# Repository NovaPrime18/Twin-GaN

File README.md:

# Twin-GaN

**Dual 3-phase GaN motor controller with on-board CAN traction control**

---

## Overview

Twin-GaN is an open-source, dual-motor VESC-compatible controller that fits two complete 3-phase inverters onto a single 99 × 99 mm board. It targets the same use case as a pair of off-the-shelf single ESCs — a two-wheel-drive skateboard, e-bike or robot — doing the job of two drivers with one board. It is **cheaper than the equivalent Flipsky dual, smaller, and more efficient**; the trade-off is deliberate, since it gives up peak power for that density. This is a 20 A-input board, not a 100 A one, and the density comes from switching to GaN rather than from oversizing the power stage.

Built around six EPC23102 eGaN ePower Stage ICs (100 V, 5.2 mΩ, gate driver and bootstrap integrated in a 3.5 × 5 mm package) and two STM32F405RGT6s, it accepts up to 60 VDC through a single XT60 and drives two motors through MR30PW-M connectors.

Both channels have their own MCU, their own USB-C port and their own three-shunt sensing chain, and all three controllers on the board (both STM32s plus an ESP32-C3-WROOM-02) share one internal CAN bus — which is what makes **traction control between the two channels** possible on-board, instead of two separate ESCs having to agree over a cable.

---

## Specifications

| Parameter | Value |
|---|---|
| Input voltage | up to 60 VDC |
| Battery input current | 20 A |
| Phase current | 20 A continuous / 40 A absolute max |
| Max input power | ≈ 1.2 kW (battery-limited: 60 V × 20 A, both channels) |
| PWM frequency | up to 35 kHz |
| Topology | 2 × independent 3-phase inverter |
| Power stage | 6 × EPC23102 ePower Stage (100 V, 5.2 mΩ) |
| Control | 2 × STM32F405RGT6 + 1 × ESP32-C3-WROOM-02 |
| Input connector | XT60 |
| Motor connectors | 2 × AMASS MR30PW-M (30 A) |
| Board | 99 × 99 mm, 4 layer, 1.6 mm |
| EDA | KiCad |

> ⚠️ **The current and power figures above are design targets for Revision 1 — they have not been bench-verified.**

---

## VESC-Tool Compatibility

- **Two independent VESC targets** — each channel runs its own STM32F405RGT6 with its own 6-PWM GaN stage, so VESC Tool detects, configures and monitors them as two separate controllers (VESC 75/300-derived hardware target)
- **USB-C per controller** — `J12`/`J13` give each motor its own USB-C for VESC Tool, with a third port (`J7`) on the ESP32-C3; every port has 5.1 kΩ CC pulldowns and VBUS → 0.5 A PTC → ferrite → diode → `+5V`
- **Three-shunt current sensing** — one INA240A1D per phase (six total) across 2 mΩ 1206 shunts, REF1 = GND / REF2 = `+3V3` for true bidirectional measurement
- **Hall sensors + motor temperature** — one 6-pin JST-PH header per channel (`J4`, `J9`): GND, Hall W, Hall V, Hall U, TEMP_MOTOR
- **VESC COMM header per channel** — 8-pin JST-PH (`J5`, `J10`) on the standard VESC accessory pinout: `+5V`, `+3V3`, GND, SCK, SDA/NSS, SCL/MOSI, MISO, ADC-15
- **SWD per controller** — Tag-Connect TC2030 footprints (`J2`, `J8`), no header needed
- **CAN** — three TJA1051T/3 transceivers on one internal bus (MCU1, MCU2 and the ESP32-C3), terminated on-board; the two channels can be coordinated for traction control over CAN
- **On-board UI** — one push button and red/green status LEDs per channel

---

## Hardware

| Component | Part |
|---|---|
| MCU | 2 × STM32F405RGT6 (LQFP-64) |
| Wireless / third CAN node | ESP32-C3-WROOM-02 |
| Power stage | 6 × EPC23102 (eGaN half-bridge with integrated driver) |
| Current sense | 6 × INA240A1D across 2 mΩ 1206 shunts |
| CAN transceivers | 3 × TJA1051T/3 |
| Signal switches | 12 × 74LVC1G66 (current / voltage filter enables) |
| FET temperature | 6 × NCP15XH103 NTC (10 kΩ @ 25 °C, one per phase) |
| Logic supply | LMR16006XDDCR: Vdrive → `+5V` → `+3V3` |
| Bus protection | 20 A fuse, SMAJ58A TVS |
| Bulk storage | 8 × 100 µF 80 V, 12 × 1 µF 100 V, 6 × 4.7 µF 100 V |
| Input connector | AMASS XT60IPW-M |
| Motor connectors | 2 × AMASS MR30PW-M |
| Hall / COMM | JST PH 6-pin (×2) / 8-pin (×2) |
| USB | 3 × USB-C 16-pin |
| Debug | 2 × Tag-Connect TC2030 SWD |
| Buttons | 2 × KMR211NGLFS |
| EDA | KiCad |

---

## Acknowledgements / Based On

- [**VESC** by Benjamin Vedder](https://github.com/vedderb/bldc) — firmware target, VESC Tool compatibility and the [VESC 75/300](https://vesc-project.com/) hardware reference
- [**EPC23108 / EPC23102 ePower™ Stage ICs** by EPC](https://epc-co.com/epc/products/gan-fets-and-ics/epc23108) — power stage, and the [EPC91128 3-phase BLDC inverter reference design](https://epc-co.com/epc/portals/0/epc/documents/guides/EPC91128-EPC91131_qsg.pdf)

---

## License

Hardware design files are licensed under the **CERN Open Hardware Licence Version 2 – Strongly Reciprocal (CERN-OHL-S v2.0)**.

See [`LICENSE`](./LICENSE) for the full text, or visit [ohwr.org/cern_ohl_s_v2](https://ohwr.org/cern_ohl_s_v2.txt).

> In short: you are free to use, study, modify, and distribute this design, provided that any derivatives are released under the same licence and source files are made available.

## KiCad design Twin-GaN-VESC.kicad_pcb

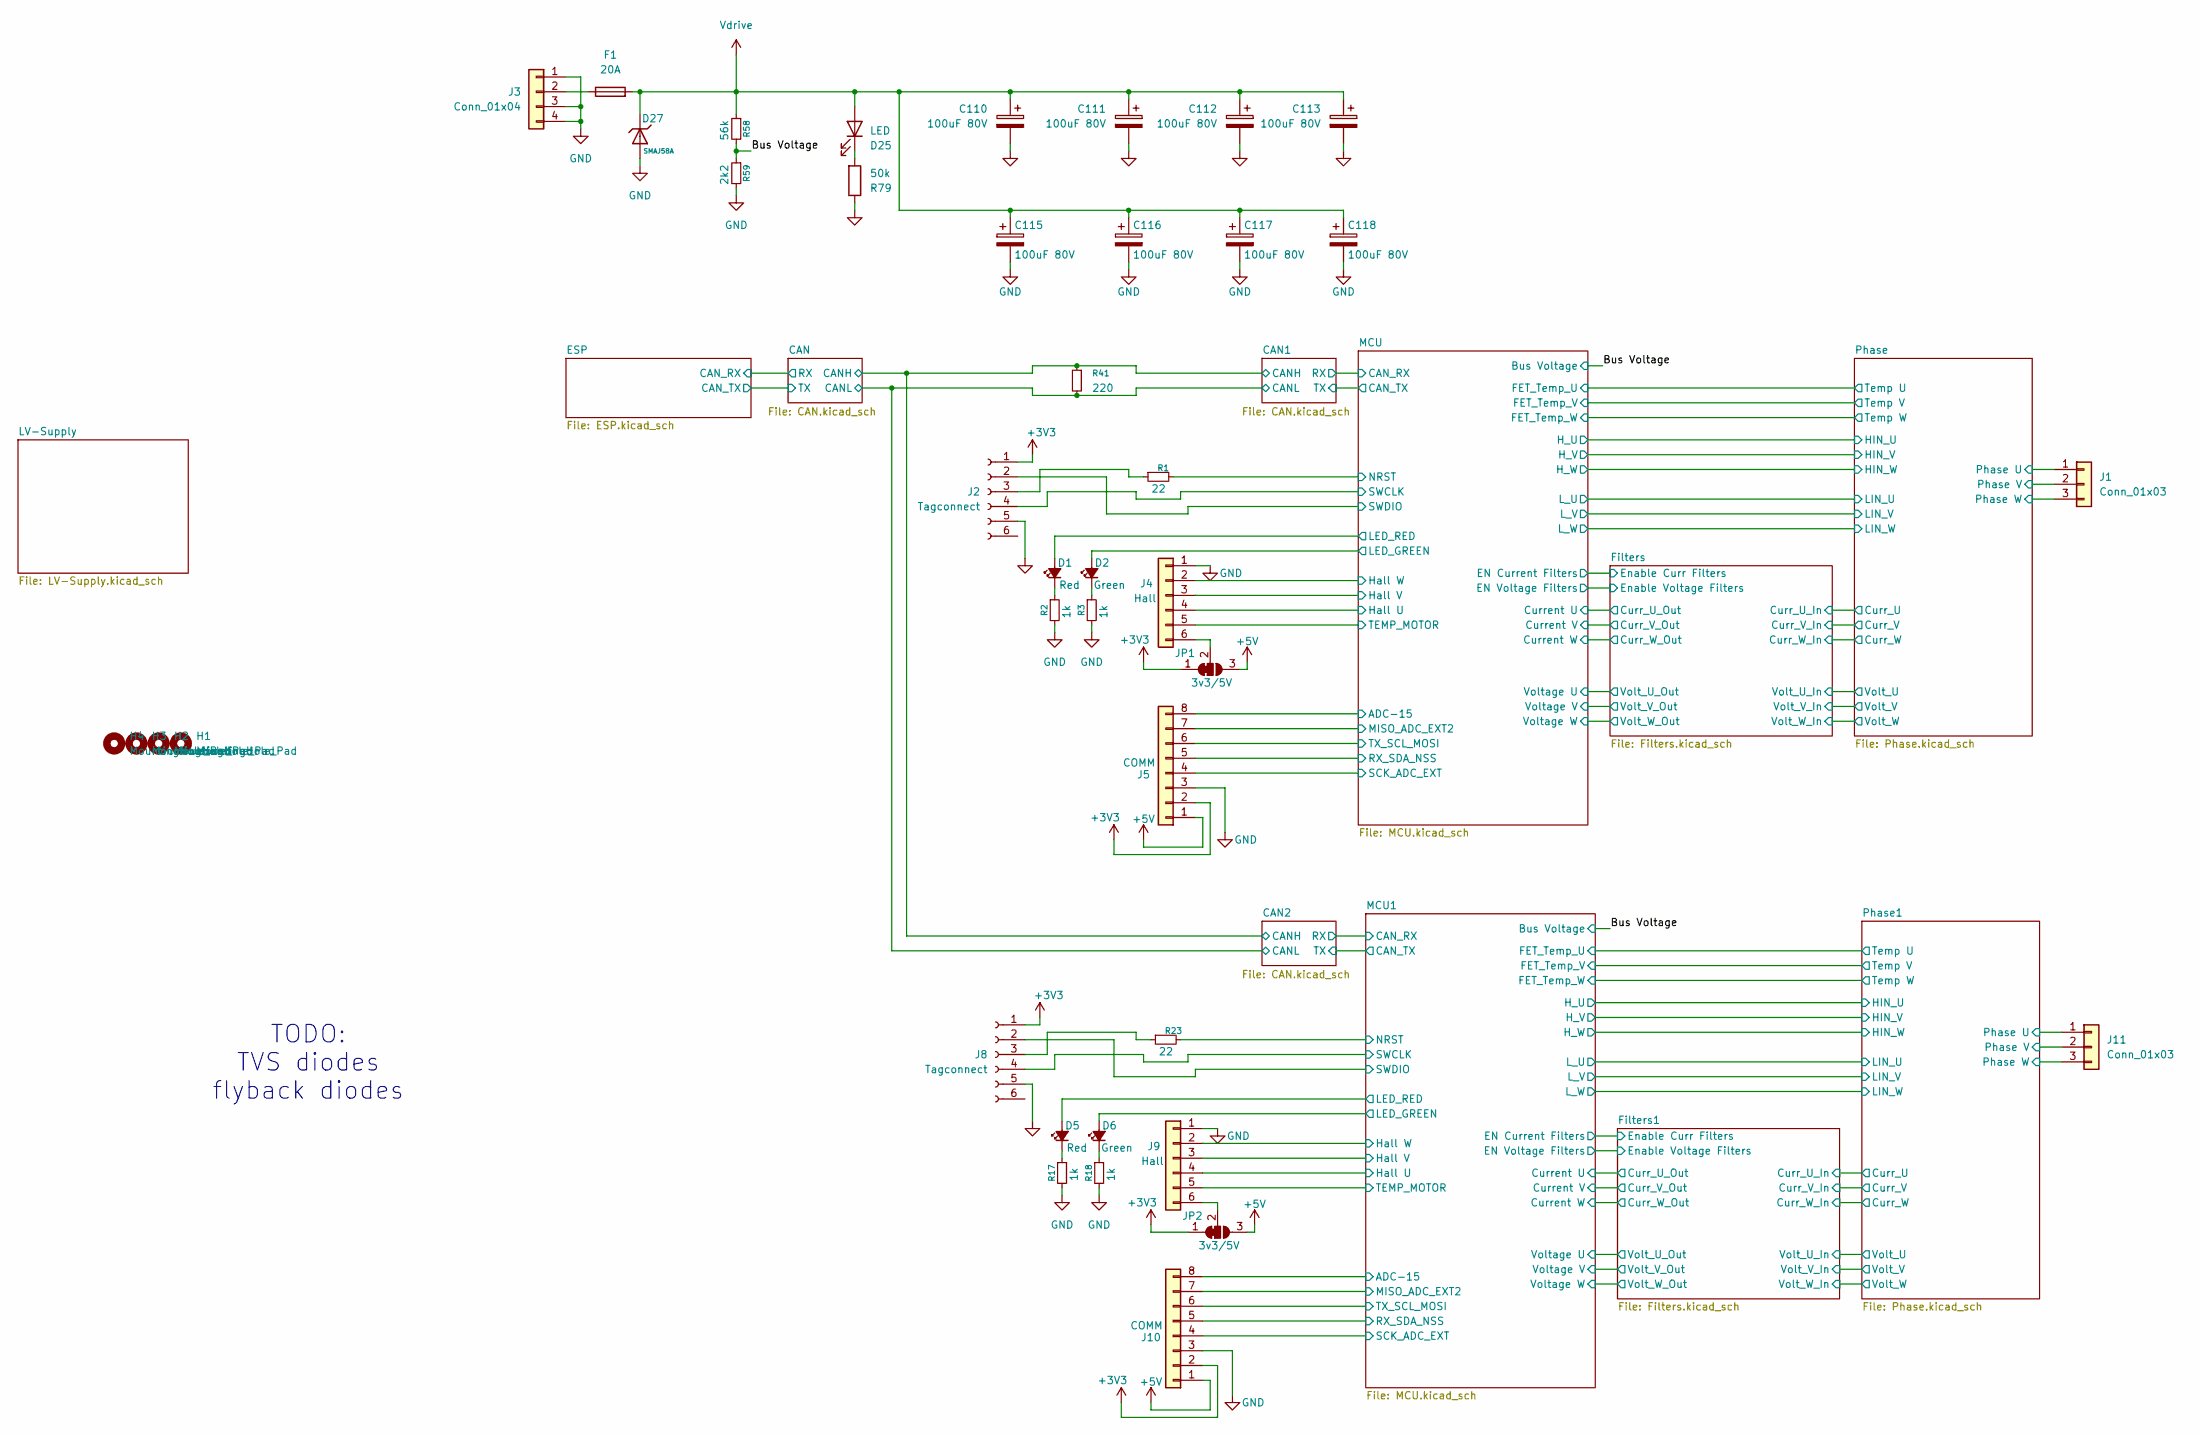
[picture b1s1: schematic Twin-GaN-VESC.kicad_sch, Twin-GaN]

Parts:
C110, C111, C112, C113, C115, C116, C117, C118: 100uF 80V; CP_Elec_10x10; LCSC C487410
D1, D5: Red; LED_0603_1608Metric; LCSC C2286
D2, D6: Green; LED_0603_1608Metric; LCSC C84267
D25: LED; LED_0603_1608Metric; LCSC C2286
D27: SMAJ58A; D_SMA; Part SMAJ58A; LCSC C19077554
F1: 20A; Fuse_2512_6332Metric; LCSC C49269483
H1, H2, H3, H4: MountingHole_Pad; MountingHole_2.7mm_M2.5
J1, J11: Conn_01x03; AMASS_MR30PW-M_1x03_P3.50mm_Horizontal
J2, J8: Tagconnect; Tag-Connect_TC2030-IDC-NL_2x03_P1.27mm_Vertical
J3: Conn_01x04; AMASS_XT60IPW-M_1x03_P7.20mm_Horizontal
J4, J9: Hall; JST_PH_B6B-PH-SM4-TB_1x06-1MP_P2.00mm_Vertical; LCSC C471518
J5, J10: COMM; JST_PH_B8B-PH-SM4-TB_1x08-1MP_P2.00mm_Vertical; LCSC C495548
JP1, JP2: 3v3/5V; SolderJumper-3_P1.3mm_Bridged12_RoundedPad1.0x1.5mm
R1, R23: 22; R_0402_1005Metric; LCSC C25092
R2, R3, R17, R18: 1k; R_0402_1005Metric; LCSC C11702
R41: 220; R_0603_1608Metric; LCSC C22962
R58: 56k; R_0603_1608Metric; LCSC C23206
R59: 2k2; R_0402_1005Metric; LCSC C25879
R79: 50k; R_0402_1005Metric; LCSC C25897

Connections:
+3V3: J2.1, J5.2, J8.1, J10.2, JP1.1 (A), JP2.1 (A); also elsewhere on the board
+5V: J5.1, J10.1, JP1.3 (B), JP2.3 (B); also elsewhere on the board
/Bus Voltage: R58.2, R59.1; also elsewhere on the board
/CAN/CANH: R41.1; also elsewhere on the board
/CAN/CANL: R41.2; also elsewhere on the board
/MCU1/ADC-15: J10.8; also elsewhere on the board
/MCU1/Hall U: J9.4; also elsewhere on the board
/MCU1/Hall V: J9.3; also elsewhere on the board
/MCU1/Hall W: J9.2; also elsewhere on the board
/MCU1/LED_GREEN: D6.2 (A); also elsewhere on the board
/MCU1/LED_RED: D5.2 (A); also elsewhere on the board
/MCU1/MISO_ADC_EXT2: J10.7; also elsewhere on the board
/MCU1/NRST: R23.2; also elsewhere on the board
/MCU1/RX_SDA_NSS: J10.5; also elsewhere on the board
/MCU1/SCK_ADC_EXT: J10.4; also elsewhere on the board
/MCU1/SWCLK: J8.4; also elsewhere on the board
/MCU1/SWDIO: J8.2; also elsewhere on the board
/MCU1/TEMP_MOTOR: J9.5; also elsewhere on the board
/MCU1/TX_SCL_MOSI: J10.6; also elsewhere on the board
/MCU/ADC-15: J5.8; also elsewhere on the board
/MCU/Hall U: J4.4; also elsewhere on the board
/MCU/Hall V: J4.3; also elsewhere on the board
/MCU/Hall W: J4.2; also elsewhere on the board
/MCU/LED_GREEN: D2.2 (A); also elsewhere on the board
/MCU/LED_RED: D1.2 (A); also elsewhere on the board
/MCU/MISO_ADC_EXT2: J5.7; also elsewhere on the board
/MCU/NRST: R1.2; also elsewhere on the board
/MCU/RX_SDA_NSS: J5.5; also elsewhere on the board
/MCU/SCK_ADC_EXT: J5.4; also elsewhere on the board
/MCU/SWCLK: J2.4; also elsewhere on the board
/MCU/SWDIO: J2.2; also elsewhere on the board
/MCU/TEMP_MOTOR: J4.5; also elsewhere on the board
/MCU/TX_SCL_MOSI: J5.6; also elsewhere on the board
/Phase1/Phase U: J11.1; also elsewhere on the board
/Phase1/Phase V: J11.2; also elsewhere on the board
/Phase1/Phase W: J11.3; also elsewhere on the board
/Phase/Phase U: J1.1; also elsewhere on the board
/Phase/Phase V: J1.2; also elsewhere on the board
/Phase/Phase W: J1.3; also elsewhere on the board
GND: C110.2, C111.2, C112.2, C113.2, C115.2, C116.2, C117.2, C118.2, D27.2, J2.5, J3.1, J3.3, J3.4, J4.1, J5.3, J8.5, J9.1, J10.3, R2.2, R3.2, R17.2, R18.2, R59.2, R79.1; also elsewhere on the board
unnamed: D1.1 (K), R2.1
unnamed: D2.1 (K), R3.1
unnamed: D5.1 (K), R17.1
unnamed: D6.1 (K), R18.1
unnamed: D25.1 (K), R79.2
unnamed: J2.3, R1.1
unnamed: F1.1, J3.2
unnamed: J4.6, JP1.2 (C)
unnamed: J8.3, R23.1
unnamed: J9.6, JP2.2 (C)
Vdrive: C110.1, C111.1, C112.1, C113.1, C115.1, C116.1, C117.1, C118.1, D25.2 (A), D27.1, F1.2, R58.1; also elsewhere on the board

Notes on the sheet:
TODO: TVS diodes flyback diodes

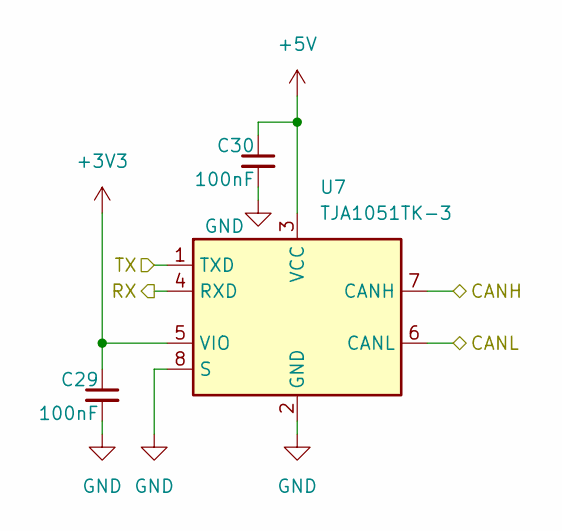
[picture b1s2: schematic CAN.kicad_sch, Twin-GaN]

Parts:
C29, C30: 100nF; C_0402_1005Metric; LCSC C307331
U7: TJA1051TK-3; HVSON-8-1EP_3x3mm_P0.65mm_EP1.6x2.4mm; JLC C2875699

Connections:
+3V3: C29.1, U7.5 (VIO); also elsewhere on the board
+5V: C30.1, U7.3 (VCC); also elsewhere on the board
/CAN/CANH: U7.7 (CANH); also elsewhere on the board
/CAN/CANL: U7.6 (CANL); also elsewhere on the board
/CAN/RX: U7.4 (RXD); also elsewhere on the board
/CAN/TX: U7.1 (TXD); also elsewhere on the board
GND: C29.2, C30.2, U7.2 (GND), U7.8 (S), U7.9 (GND); also elsewhere on the board

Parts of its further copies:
C106, C107, C108, C109: 100nF; C_0402_1005Metric; LCSC C307331
U31, U32: TJA1051TK-3; HVSON-8-1EP_3x3mm_P0.65mm_EP1.6x2.4mm; JLC C2875699

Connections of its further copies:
+3V3: C106.1, C108.1, U31.5 (VIO), U32.5 (VIO); also elsewhere on the board
+5V: C107.1, C109.1, U31.3 (VCC), U32.3 (VCC); also elsewhere on the board
/CAN1/RX: U31.4 (RXD); also elsewhere on the board
/CAN1/TX: U31.1 (TXD); also elsewhere on the board
/CAN2/RX: U32.4 (RXD); also elsewhere on the board
/CAN2/TX: U32.1 (TXD); also elsewhere on the board
/CAN/CANH: U31.7 (CANH), U32.7 (CANH); also elsewhere on the board
/CAN/CANL: U31.6 (CANL), U32.6 (CANL); also elsewhere on the board
GND: C106.2, C107.2, C108.2, C109.2, U31.2 (GND), U31.8 (S), U31.9 (GND), U32.2 (GND), U32.8 (S), U32.9 (GND); also elsewhere on the board

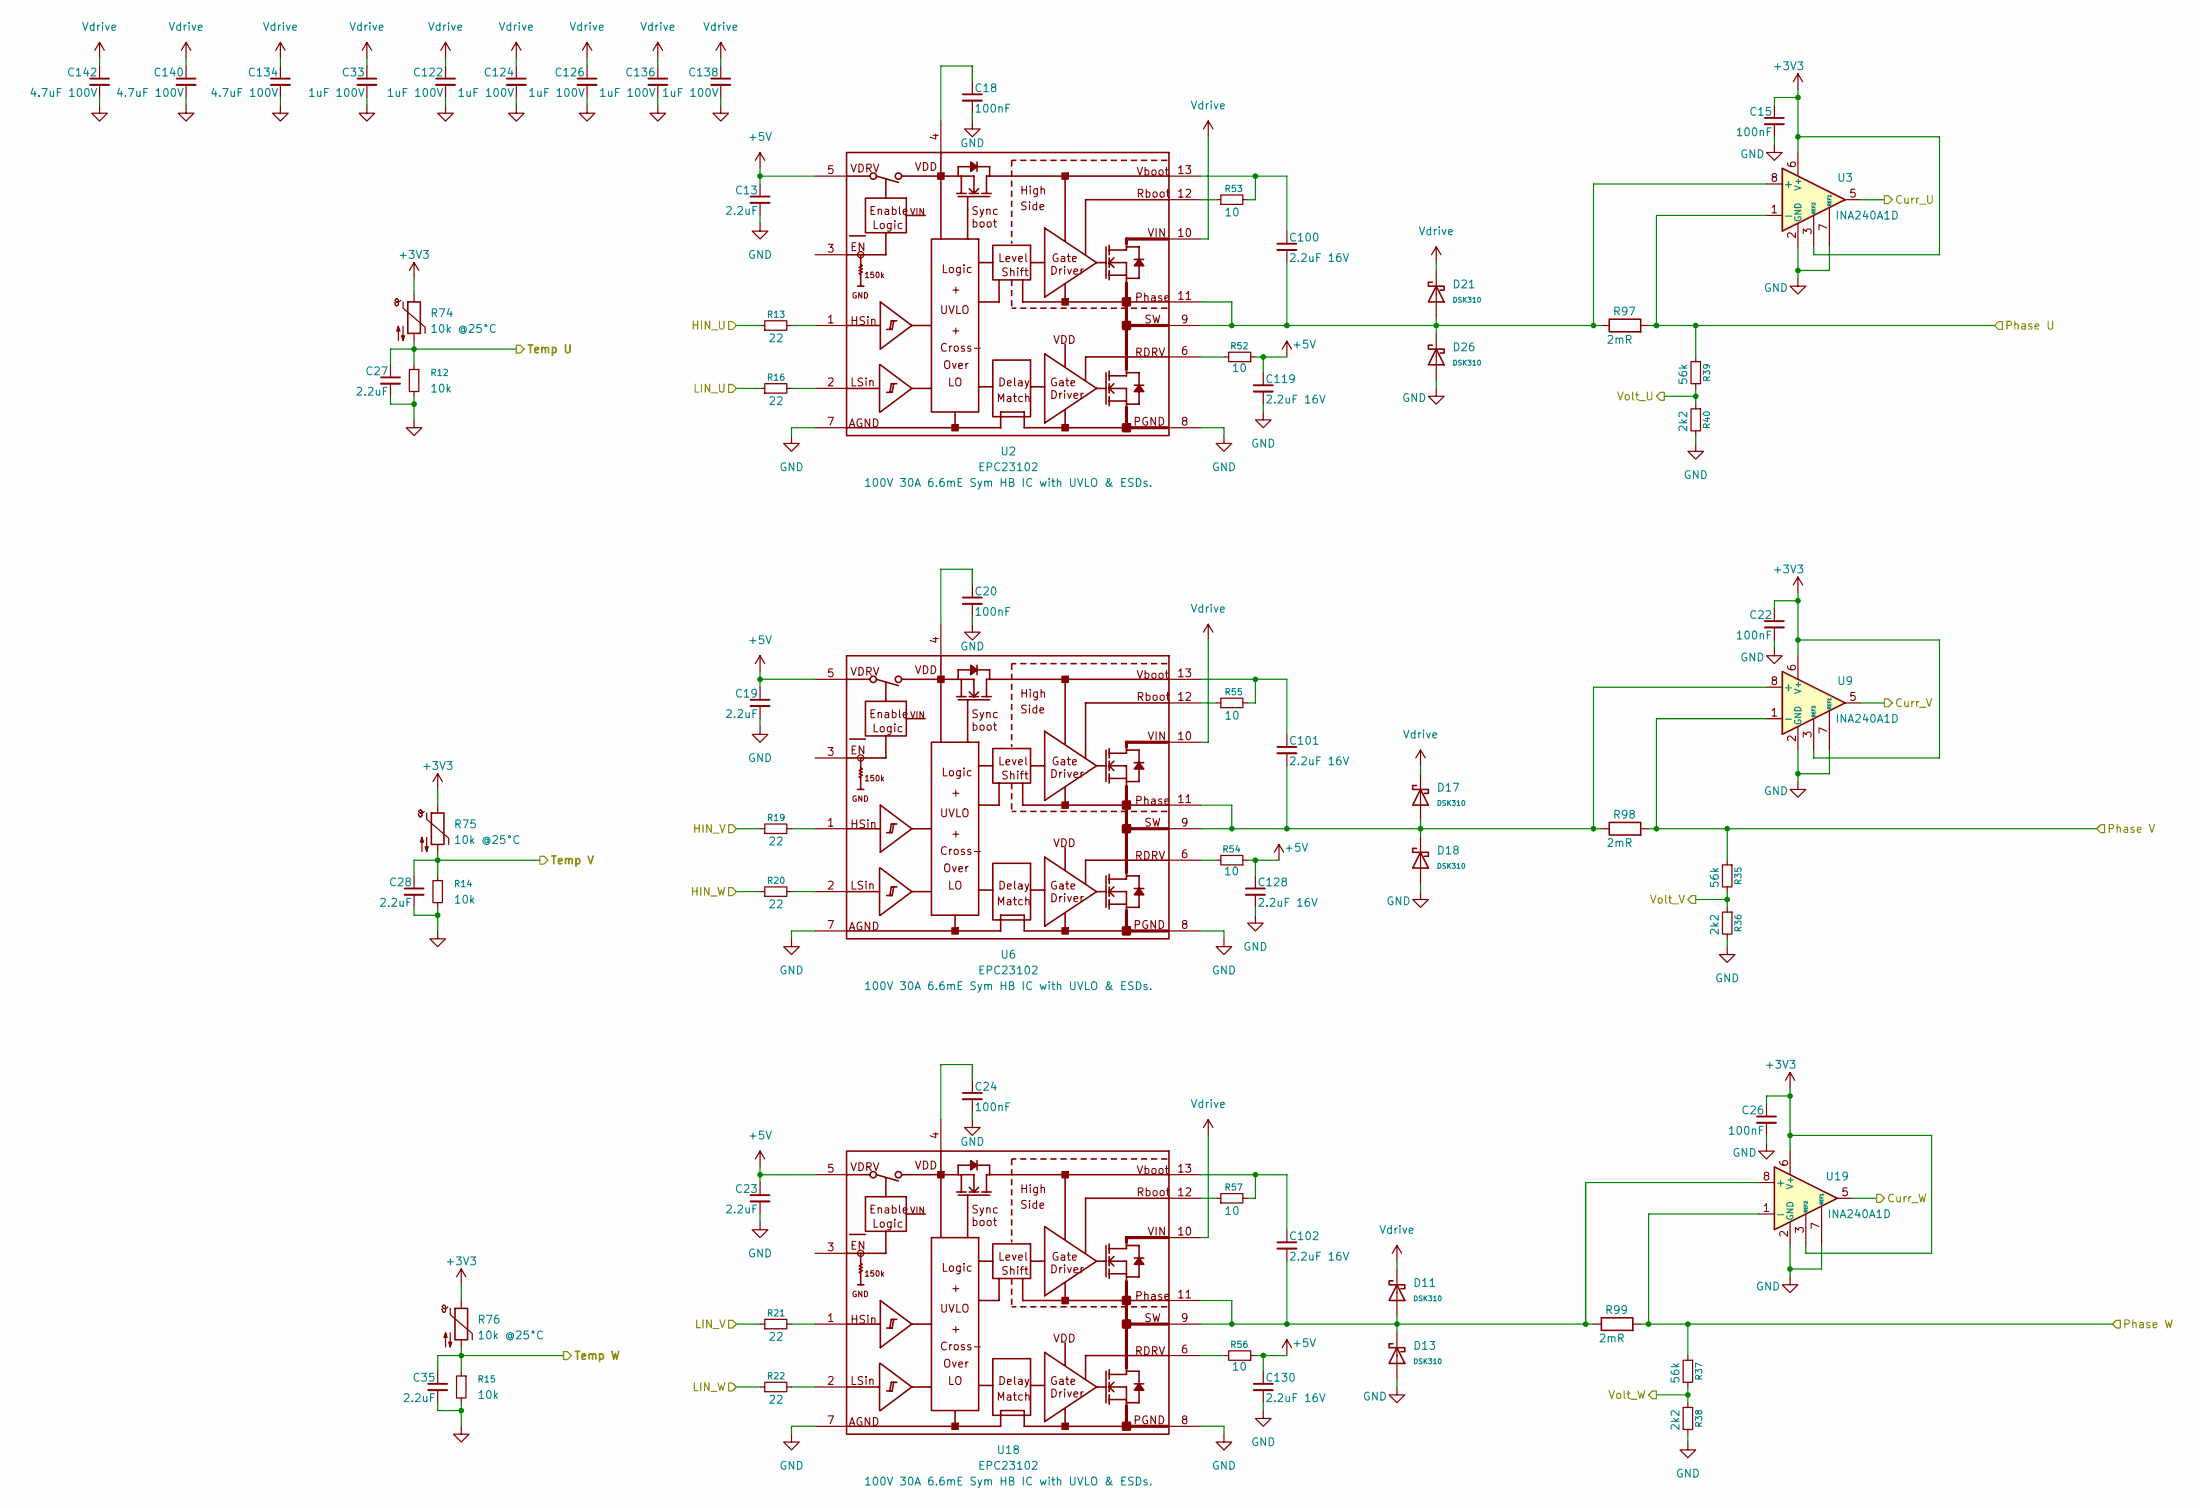
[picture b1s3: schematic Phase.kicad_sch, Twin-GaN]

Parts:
C13, C19, C23, C27, C28, C35: 2.2uF; C_0402_1005Metric; LCSC C20539421
C15, C18, C20, C22, C24, C26: 100nF; C_0402_1005Metric; LCSC C307331
C33, C122, C124, C126, C136, C138: 1uF 100V; C_0805_2012Metric; LCSC C5370002
C100, C101, C102, C119, C128, C130: 2.2uF 16V; C_0402_1005Metric; LCSC C307418
C134, C140, C142: 4.7uF 100V; C_1206_3216Metric; LCSC C22367839
D11, D13, D17, D18, D21, D26: DSK310; D_SOD-123F; Part SS28; LCSC C28646289
R12, R14, R15: 10k; R_0402_1005Metric; LCSC C25744
R13, R16, R19, R20, R21, R22: 22; R_0402_1005Metric; LCSC C25092
R35, R37, R39: 56k; R_0603_1608Metric; LCSC C23206
R36, R38, R40: 2k2; R_0402_1005Metric; LCSC C25879
R52, R53, R54, R55, R56, R57: 10; R_0402_1005Metric; LCSC C25077
R74, R75, R76: 10k @25°C; R_0402_1005Metric; LCSC C77131
R97, R98, R99: 2mR; R_1206_3216Metric; LCSC C601094
U2, U6, U18: EPC23102; D0727
U3, U9, U19: INA240A1D; SOIC-8_3.9x4.9mm_P1.27mm; LCSC C1346458

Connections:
+3V3: C15.1, C22.1, C26.1, R74.1, R75.1, R76.1, U3.3 (REF2), U3.6 (V+), U9.3 (REF2), U9.6 (V+), U19.3 (REF2), U19.6 (V+); also elsewhere on the board
+5V: C13.1, C19.1, C23.1, C119.1, C128.1, C130.1, R52.1, R54.1, R56.1, U2.5 (VDRV), U6.5 (VDRV), U18.5 (VDRV); also elsewhere on the board
/Filters/Curr_U_In: U3.5; also elsewhere on the board
/Filters/Curr_V_In: U9.5; also elsewhere on the board
/Filters/Curr_W_In: U19.5; also elsewhere on the board
/Filters/Volt_U_In: R39.2, R40.1; also elsewhere on the board
/Filters/Volt_V_In: R35.2, R36.1; also elsewhere on the board
/Filters/Volt_W_In: R37.2, R38.1; also elsewhere on the board
/MCU/FET_Temp_U: C27.1, R12.1, R74.2; also elsewhere on the board
/MCU/FET_Temp_V: C28.1, R14.1, R75.2; also elsewhere on the board
/MCU/FET_Temp_W: C35.1, R15.1, R76.2; also elsewhere on the board
/MCU/H_U: R13.1; also elsewhere on the board
/MCU/H_V: R19.1; also elsewhere on the board
/MCU/H_W: R20.1; also elsewhere on the board
/MCU/L_U: R16.1; also elsewhere on the board
/MCU/L_V: R21.1; also elsewhere on the board
/MCU/L_W: R22.1; also elsewhere on the board
/Phase/Phase U: R39.1, R97.2, U3.1 (-); also elsewhere on the board
/Phase/Phase V: R35.1, R98.2, U9.1 (-); also elsewhere on the board
/Phase/Phase W: R37.1, R99.2, U19.1 (-); also elsewhere on the board
GND: C13.2, C15.2, C18.2, C19.2, C20.2, C22.2, C23.2, C24.2, C26.2, C27.2, C28.2, C33.2, C35.2, C119.2, C122.2, C124.2, C126.2, C128.2, C130.2, C134.2, C136.2, C138.2, C140.2, C142.2, D13.2, D18.2, D26.2, R12.2, R14.2, R15.2, R36.2, R38.2, R40.2, U2.7 (AGND), U2.8 (PGND), U3.2 (GND), U3.4 (GND), U3.7 (REF1), U6.7 (AGND), U6.8 (PGND), U9.2 (GND), U9.4 (GND), U9.7 (REF1), U18.7 (AGND), U18.8 (PGND), U19.2 (GND), U19.4 (GND), U19.7 (REF1); also elsewhere on the board
unnamed: R13.2, U2.1 (HSin)
unnamed: R16.2, U2.2 (LSin)
unnamed: C100.2, D21.2, D26.1, R97.1, U2.9 (SW), U2.11 (Phase), U3.8 (+)
unnamed: R52.2, U2.6 (RDRV)
unnamed: R53.1, U2.12 (Rboot)
unnamed: C18.1, U2.4 (VDD)
unnamed: C100.1, R53.2, U2.13 (Vboot)
unnamed: R19.2, U6.1 (HSin)
unnamed: R20.2, U6.2 (LSin)
unnamed: C101.2, D17.2, D18.1, R98.1, U6.9 (SW), U6.11 (Phase), U9.8 (+)
unnamed: R54.2, U6.6 (RDRV)
unnamed: R55.1, U6.12 (Rboot)
unnamed: C20.1, U6.4 (VDD)
unnamed: C101.1, R55.2, U6.13 (Vboot)
unnamed: R21.2, U18.1 (HSin)
unnamed: R22.2, U18.2 (LSin)
unnamed: C102.2, D11.2, D13.1, R99.1, U18.9 (SW), U18.11 (Phase), U19.8 (+)
unnamed: R56.2, U18.6 (RDRV)
unnamed: R57.1, U18.12 (Rboot)
unnamed: C24.1, U18.4 (VDD)
unnamed: C102.1, R57.2, U18.13 (Vboot)
Vdrive: C33.1, C122.1, C124.1, C126.1, C134.1, C136.1, C138.1, C140.1, C142.1, D11.1, D17.1, D21.1, U2.10 (VIN), U6.10 (VIN), U18.10 (VIN); also elsewhere on the board

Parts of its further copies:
C46, C85, C89, C94, C95, C96: 2.2uF; C_0402_1005Metric; LCSC C20539421
C97, C98, C99, C103, C104, C105: 100nF; C_0402_1005Metric; LCSC C307331
C114, C120, C129, C131, C132, C133: 2.2uF 16V; C_0402_1005Metric; LCSC C307418
C121, C123, C125, C127, C137, C139: 1uF 100V; C_0805_2012Metric; LCSC C5370002
C135, C141, C143: 4.7uF 100V; C_1206_3216Metric; LCSC C22367839
D12, D15, D19, D20, D28, D29: DSK310; D_SOD-123F; Part SS28; LCSC C28646289
R32, R33, R34: 10k; R_0402_1005Metric; LCSC C25744
R60, R61, R62, R63, R64, R65: 22; R_0402_1005Metric; LCSC C25092
R66, R69, R70, R71, R87, R88: 10; R_0402_1005Metric; LCSC C25077
R81, R82, R83: 10k @25°C; R_0402_1005Metric; LCSC C77131
R89, R91, R103: 56k; R_0603_1608Metric; LCSC C23206
R90, R96, R104: 2k2; R_0402_1005Metric; LCSC C25879
R100, R101, R102: 2mR; R_1206_3216Metric; LCSC C601094
U5, U26, U27: EPC23102; D0727
U28, U29, U30: INA240A1D; SOIC-8_3.9x4.9mm_P1.27mm; LCSC C1346458

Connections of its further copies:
+3V3: C103.1, C104.1, C105.1, R81.1, R82.1, R83.1, U28.3 (REF2), U28.6 (V+), U29.3 (REF2), U29.6 (V+), U30.3 (REF2), U30.6 (V+); also elsewhere on the board
+5V: C94.1, C95.1, C96.1, C120.1, C129.1, C131.1, R66.1, R69.1, R70.1, U5.5 (VDRV), U26.5 (VDRV), U27.5 (VDRV); also elsewhere on the board
/Filters1/Curr_U_In: U28.5; also elsewhere on the board
/Filters1/Curr_V_In: U29.5; also elsewhere on the board
/Filters1/Curr_W_In: U30.5; also elsewhere on the board
/Filters1/Volt_U_In: R89.2, R90.1; also elsewhere on the board
/Filters1/Volt_V_In: R103.2, R104.1; also elsewhere on the board
/Filters1/Volt_W_In: R91.2, R96.1; also elsewhere on the board
/MCU1/FET_Temp_U: C46.1, R32.1, R81.2; also elsewhere on the board
/MCU1/FET_Temp_V: C85.1, R33.1, R82.2; also elsewhere on the board
/MCU1/FET_Temp_W: C89.1, R34.1, R83.2; also elsewhere on the board
/MCU1/H_U: R60.1; also elsewhere on the board
/MCU1/H_V: R62.1; also elsewhere on the board
/MCU1/H_W: R63.1; also elsewhere on the board
/MCU1/L_U: R61.1; also elsewhere on the board
/MCU1/L_V: R64.1; also elsewhere on the board
/MCU1/L_W: R65.1; also elsewhere on the board
/Phase1/Phase U: R89.1, R100.2, U28.1 (-); also elsewhere on the board
/Phase1/Phase V: R101.2, R103.1, U29.1 (-); also elsewhere on the board
/Phase1/Phase W: R91.1, R102.2, U30.1 (-); also elsewhere on the board
GND: C46.2, C85.2, C89.2, C94.2, C95.2, C96.2, C97.2, C98.2, C99.2, C103.2, C104.2, C105.2, C120.2, C121.2, C123.2, C125.2, C127.2, C129.2, C131.2, C135.2, C137.2, C139.2, C141.2, C143.2, D15.2, D20.2, D29.2, R32.2, R33.2, R34.2, R90.2, R96.2, R104.2, U5.7 (AGND), U5.8 (PGND), U26.7 (AGND), U26.8 (PGND), U27.7 (AGND), U27.8 (PGND), U28.2 (GND), U28.4 (GND), U28.7 (REF1), U29.2 (GND), U29.4 (GND), U29.7 (REF1), U30.2 (GND), U30.4 (GND), U30.7 (REF1); also elsewhere on the board
unnamed: R60.2, U5.1 (HSin)
unnamed: R61.2, U5.2 (LSin)
unnamed: R66.2, U5.6 (RDRV)
unnamed: R71.1, U5.12 (Rboot)
unnamed: C97.1, U5.4 (VDD)
unnamed: C114.1, R71.2, U5.13 (Vboot)
unnamed: R62.2, U26.1 (HSin)
unnamed: R63.2, U26.2 (LSin)
unnamed: C132.2, D19.2, D20.1, R101.1, U26.9 (SW), U26.11 (Phase), U29.8 (+)
unnamed: R69.2, U26.6 (RDRV)
unnamed: R87.1, U26.12 (Rboot)
unnamed: C98.1, U26.4 (VDD)
unnamed: C132.1, R87.2, U26.13 (Vboot)
unnamed: R64.2, U27.1 (HSin)
unnamed: R65.2, U27.2 (LSin)
unnamed: C133.2, D12.2, D15.1, R102.1, U27.9 (SW), U27.11 (Phase), U30.8 (+)
unnamed: R70.2, U27.6 (RDRV)
unnamed: R88.1, U27.12 (Rboot)
unnamed: C99.1, U27.4 (VDD)
unnamed: C133.1, R88.2, U27.13 (Vboot)
unnamed: C114.2, D28.2, D29.1, R100.1, U5.9 (SW), U5.11 (Phase), U28.8 (+)
Vdrive: C121.1, C123.1, C125.1, C127.1, C135.1, C137.1, C139.1, C141.1, C143.1, D12.1, D19.1, D28.1, U5.10 (VIN), U26.10 (VIN), U27.10 (VIN); also elsewhere on the board

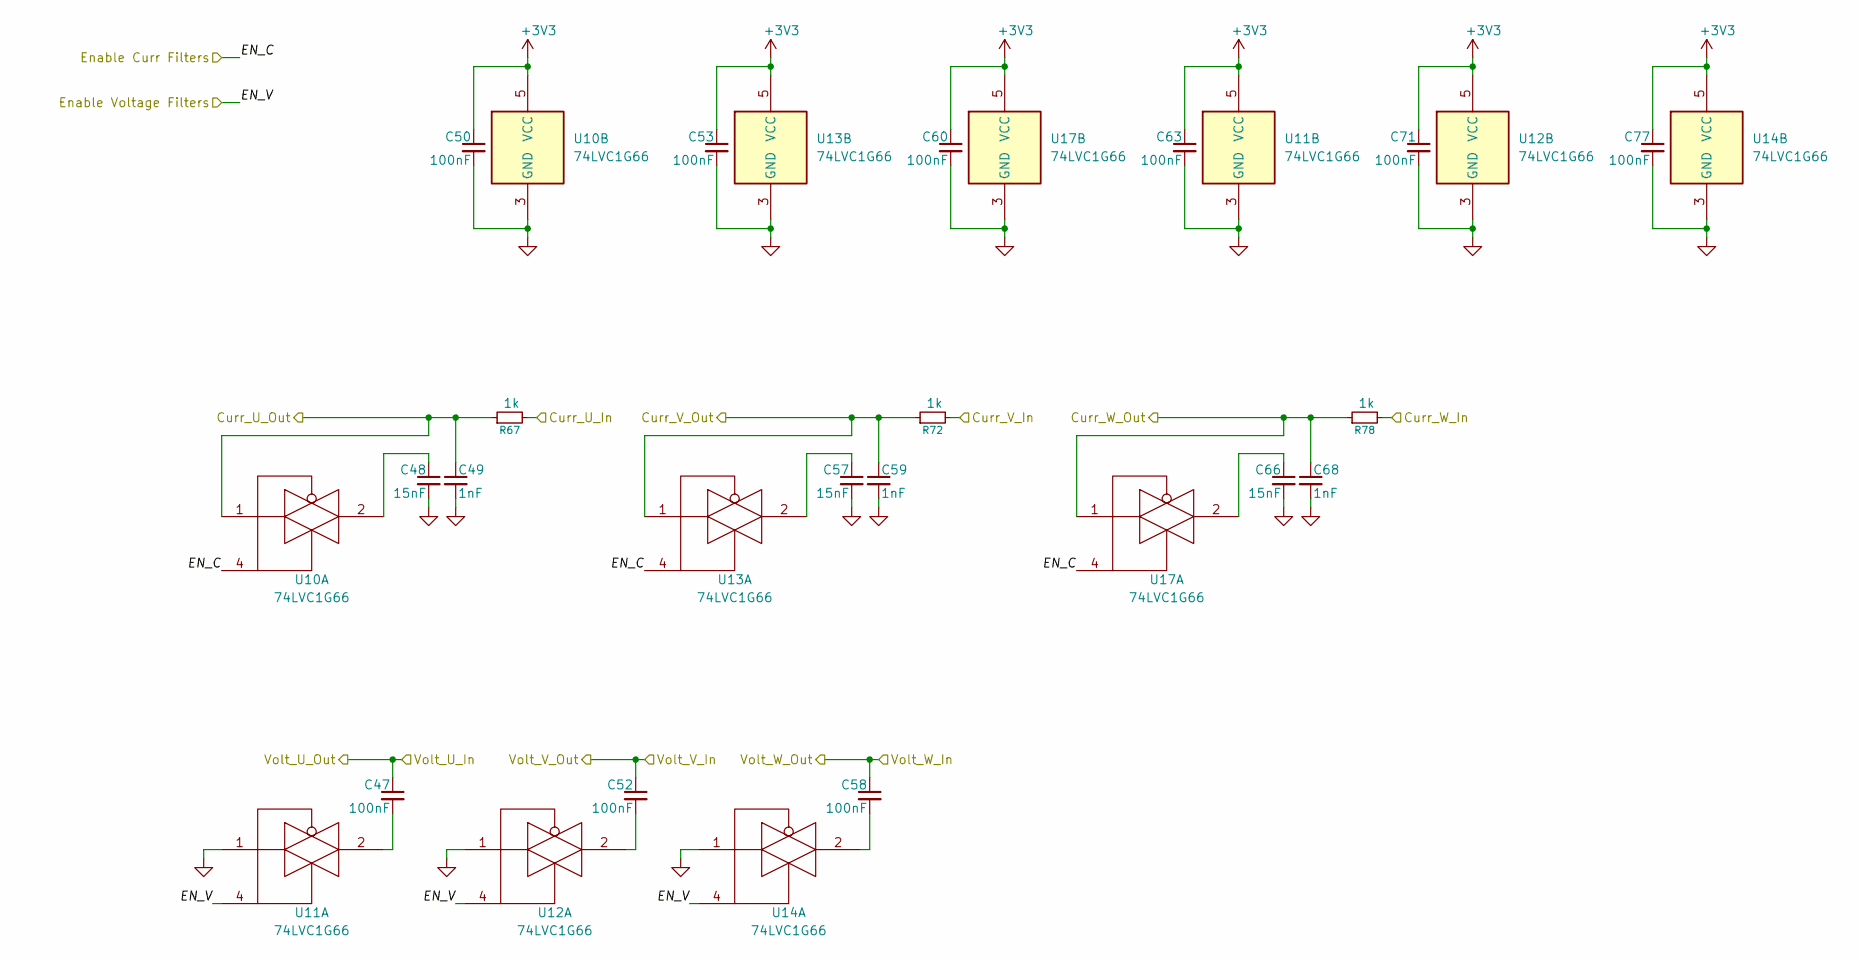
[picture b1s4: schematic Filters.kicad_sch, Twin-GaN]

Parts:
C47, C50, C52, C53, C58, C60, C63, C71, C77: 100nF; C_0402_1005Metric; LCSC C307331
C48, C57, C66: 15nF; C_0402_1005Metric; LCSC C114405
C49, C59, C68: 1nF; C_0402_1005Metric; LCSC C1523
R67, R72, R78: 1k; R_0402_1005Metric; LCSC C11702
U10, U11, U12, U13, U14, U17: 74LVC1G66; SOT-353_SC-70-5; JLC C97489

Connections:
+3V3: C50.1, C53.1, C60.1, C63.1, C71.1, C77.1, U10.5 (VCC), U11.5 (VCC), U12.5 (VCC), U13.5 (VCC), U14.5 (VCC), U17.5 (VCC); also elsewhere on the board
/Filters/Curr_U_In: R67.2; also elsewhere on the board
/Filters/Curr_U_Out: C49.1, R67.1, U10.1; also elsewhere on the board
/Filters/Curr_V_In: R72.2; also elsewhere on the board
/Filters/Curr_V_Out: C59.1, R72.1, U13.1; also elsewhere on the board
/Filters/Curr_W_In: R78.2; also elsewhere on the board
/Filters/Curr_W_Out: C68.1, R78.1, U17.1; also elsewhere on the board
/Filters/EN_C: U10.4, U13.4, U17.4; also elsewhere on the board
/Filters/EN_V: U11.4, U12.4, U14.4; also elsewhere on the board
/Filters/Volt_U_In: C47.1; also elsewhere on the board
/Filters/Volt_V_In: C52.1; also elsewhere on the board
/Filters/Volt_W_In: C58.1; also elsewhere on the board
GND: C48.2, C49.2, C50.2, C53.2, C57.2, C59.2, C60.2, C63.2, C66.2, C68.2, C71.2, C77.2, U10.3 (GND), U11.1, U11.3 (GND), U12.1, U12.3 (GND), U13.3 (GND), U14.1, U14.3 (GND), U17.3 (GND); also elsewhere on the board
unnamed: C47.2, U11.2
unnamed: C48.1, U10.2
unnamed: C52.2, U12.2
unnamed: C57.1, U13.2
unnamed: C58.2, U14.2
unnamed: C66.1, U17.2

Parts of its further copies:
C51, C70, C73, C74, C76, C79, C80, C83, C84: 100nF; C_0402_1005Metric; LCSC C307331
C54, C75, C81: 15nF; C_0402_1005Metric; LCSC C114405
C67, C78, C82: 1nF; C_0402_1005Metric; LCSC C1523
R68, R73, R80: 1k; R_0402_1005Metric; LCSC C11702
U20, U21, U22, U23, U24, U25: 74LVC1G66; SOT-353_SC-70-5; JLC C97489

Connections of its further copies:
+3V3: C70.1, C74.1, C79.1, C80.1, C83.1, C84.1, U20.5 (VCC), U21.5 (VCC), U22.5 (VCC), U23.5 (VCC), U24.5 (VCC), U25.5 (VCC); also elsewhere on the board
/Filters1/Curr_U_In: R68.2; also elsewhere on the board
/Filters1/Curr_U_Out: C67.1, R68.1, U20.1; also elsewhere on the board
/Filters1/Curr_V_In: R73.2; also elsewhere on the board
/Filters1/Curr_V_Out: C78.1, R73.1, U23.1; also elsewhere on the board
/Filters1/Curr_W_In: R80.2; also elsewhere on the board
/Filters1/Curr_W_Out: C82.1, R80.1, U25.1; also elsewhere on the board
/Filters1/EN_C: U20.4, U23.4, U25.4; also elsewhere on the board
/Filters1/EN_V: U21.4, U22.4, U24.4; also elsewhere on the board
/Filters1/Volt_U_In: C51.1; also elsewhere on the board
/Filters1/Volt_V_In: C73.1; also elsewhere on the board
/Filters1/Volt_W_In: C76.1; also elsewhere on the board
GND: C54.2, C67.2, C70.2, C74.2, C75.2, C78.2, C79.2, C80.2, C81.2, C82.2, C83.2, C84.2, U20.3 (GND), U21.1, U21.3 (GND), U22.1, U22.3 (GND), U23.3 (GND), U24.1, U24.3 (GND), U25.3 (GND); also elsewhere on the board
unnamed: C51.2, U21.2
unnamed: C54.1, U20.2
unnamed: C73.2, U22.2
unnamed: C75.1, U23.2
unnamed: C76.2, U24.2
unnamed: C81.1, U25.2

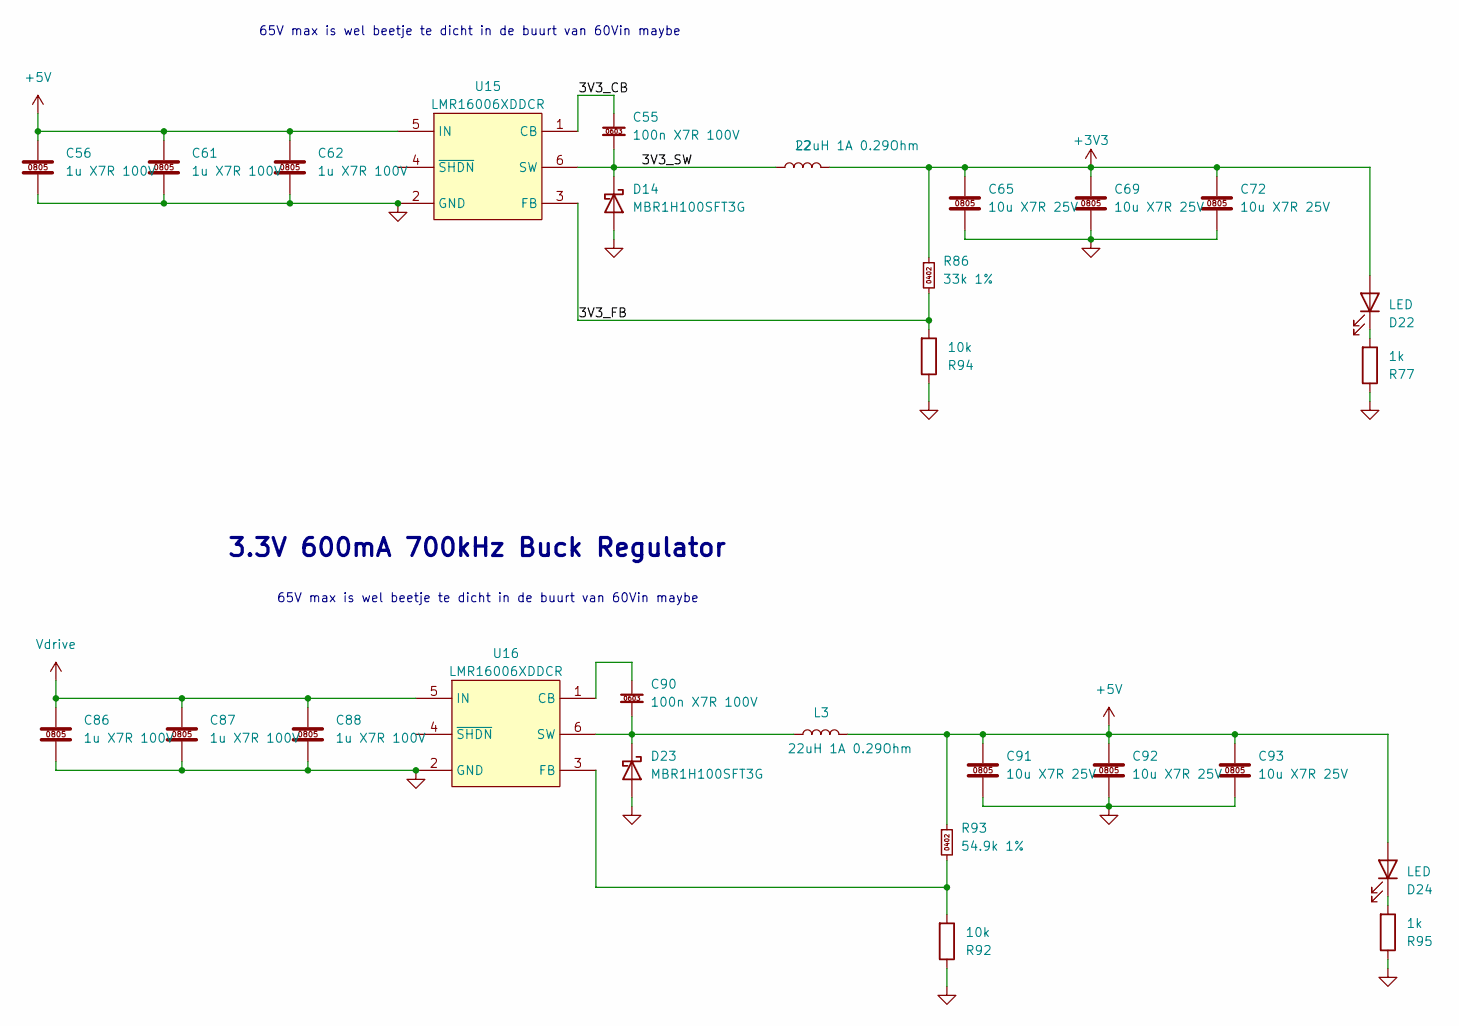
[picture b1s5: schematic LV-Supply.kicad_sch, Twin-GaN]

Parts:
C55, C90: 100n X7R 100V; C_0603_1608Metric; Manufacturer Part Number CL10B104KC8NNNC; LCSC C15725
C56, C61, C62, C86, C87, C88: 1u X7R 100V; C_0805_2012Metric; Manufacturer Part Number CC0805KKX7R0BB105; LCSC C5370002
C65, C69, C72, C91, C92, C93: 10u X7R 25V; C_0805_2012Metric; Manufacturer Part Number CL21B106KAYQNNE; LCSC C3039694
D14, D23: MBR1H100SFT3G; D_SOD-123F; Manufacturer Part Number MBR1H100SFT3G; LCSC C235757
D22, D24: LED; LED_0603_1608Metric; LCSC C2286
L2, L3: 22uH 1A 0.29Ohm; L_Sunlord_SWPA4030S; Manufacturer Part Number SWPA4030S220MT; LCSC C167883
R77, R95: 1k; R_0402_1005Metric; LCSC C106235
R86: 33k 1%; R_0402_1005Metric; Manufacturer Part Number RC0402FR-0733KL; LCSC C138003
R92, R94: 10k; R_0402_1005Metric; LCSC C2906861
R93: 54.9k 1%; R_0402_1005Metric; LCSC C11626
U15, U16: LMR16006XDDCR; SOT-23-6; Manufacturer Part Number LMR16006XDDCR; LCSC C87080

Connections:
+3V3: C65.1, C69.1, C72.1, D22.2 (A), L2.2, R86.1; also elsewhere on the board
+5V: C56.1, C61.1, C62.1, C91.1, C92.1, C93.1, D24.2 (A), L3.2, R93.1, U15.5 (IN); also elsewhere on the board
/LV-Supply/3V3_CB: C55.1, U15.1 (CB)
/LV-Supply/3V3_FB: R86.2, R94.2, U15.3 (FB)
/LV-Supply/3V3_SW: C55.2, D14.1 (K), L2.1, U15.6 (SW)
GND: C56.2, C61.2, C62.2, C65.2, C69.2, C72.2, C86.2, C87.2, C88.2, C91.2, C92.2, C93.2, D14.2 (A), D23.2 (A), R77.1, R92.1, R94.1, R95.1, U15.2 (GND), U16.2 (GND); also elsewhere on the board
unnamed: D22.1 (K), R77.2
unnamed: C90.2, D23.1 (K), L3.1, U16.6 (SW)
unnamed: D24.1 (K), R95.2
unnamed: C90.1, U16.1 (CB)
unnamed: R92.2, R93.2, U16.3 (FB)
Vdrive: C86.1, C87.1, C88.1, U16.5 (IN); also elsewhere on the board

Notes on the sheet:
65V max is wel beetje te dicht in de buurt van 60Vin maybe
3.3V 600mA 700kHz Buck Regulator

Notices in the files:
README.md:
License: CERN-OHL-S v2.0
